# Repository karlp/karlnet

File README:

Hi! This is the karlnet source tree.
karlnet consists of nodes, which are (normally) battery powered sensor devices, transmitting data at some
interval back to a base station.  The base station handles decoding the binary wire formats, and posts all
the data onto a stomp message bus topic. (the base station is a data producer)  Then any consumer that
wishes, simply subscribes to the topic, and receives all data from the network, from the minute the
connect.

common - headers and things for packet definitions, etc
producers - software that can produce data to stick into karlnet, (xbee receiver)
consumers - software that makes use of karlnet data (rrd, webpages, etc)
nodes - firmware that runs on the wireless nodes, and the cad files for each node
eagle - shared files for eagle cad (part libraries)
experiments - uncategorized, or incomplete projects.

python dependencies:
 * Stompy: http://packages.python.org/stompy/
 * python-usb v1.x (you'll have to uninstall 0.4.x, or fiddle with sys.path)
 * python-jsonpickle

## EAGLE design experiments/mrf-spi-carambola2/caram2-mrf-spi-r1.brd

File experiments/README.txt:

1. Name: Karl Palsson

2. Company: n/a

3. Billing address: 

Karl Palsson
Hverfisgata 104c
Reykjavik, 101
Iceland

4. Shipping address: 

same as billing

5. Shipping option: airmail

6. Order: 
    1 DSS panel, panelisation image attached as:  olimex-panelisation-20110107.png

7. For all orders from Europe Union: n/a

8. Payment option: Visa

9. De-panelization with smooth or rough borders (read our FAQ for panelization
to learn what does this means)
   Smooth.  I believe my measurements are correct, and there's room for this.

10. Notes: 

    dresdonbo_v02 uses 0.6mm drills, to make sure that the pad/drill spacing meets your
design rules.

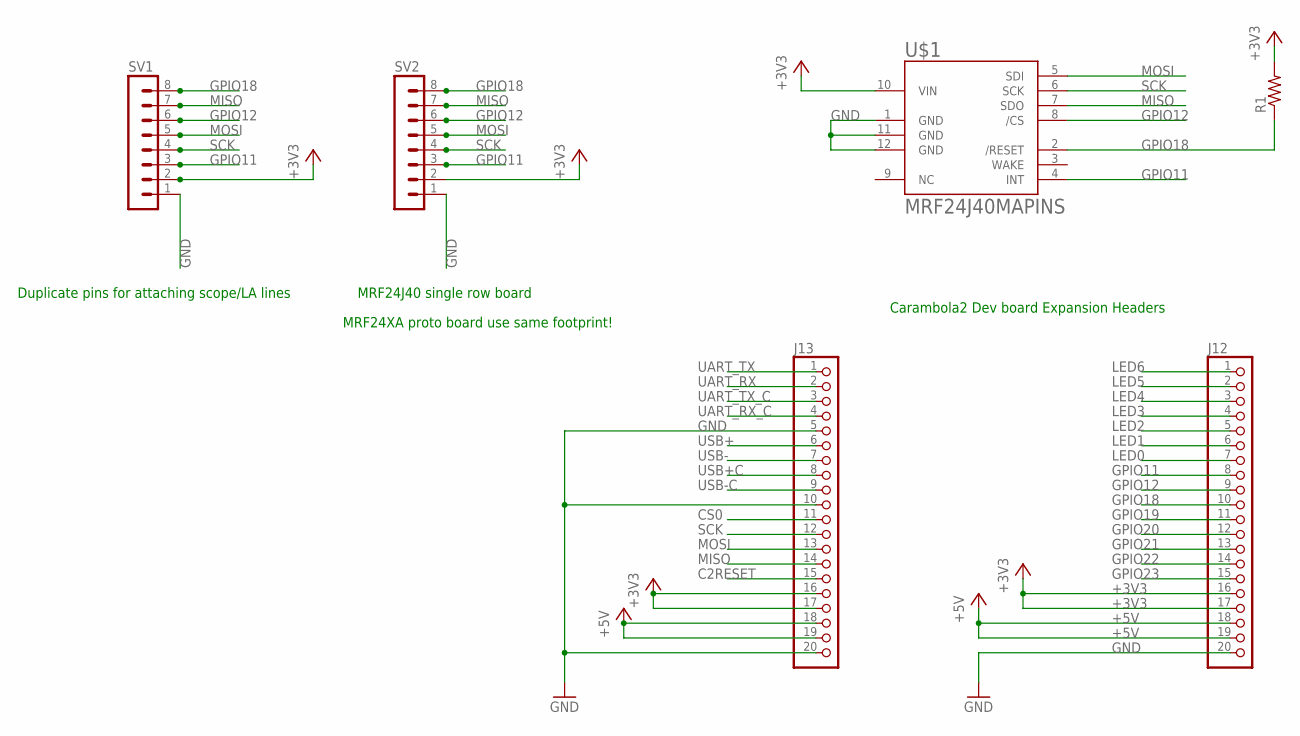
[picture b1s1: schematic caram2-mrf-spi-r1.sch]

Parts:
J12, J13: PINHD-1X20; 1X20
R1: R-US_R0805; R0805
SV1, SV2: MA08-1
U$1: MRF24J40MAPINS; MRF24J40MA

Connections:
+3V3: J12.16, J12.17, J13.16, J13.17, R1.2, SV1.2, SV2.2, U$1.10 (VIN)
+5V: J12.18, J12.19, J13.18, J13.19
C2RESET: J13.15
CS0: J13.11
GND: J12.20, J13.5, J13.10, J13.20, SV1.1, SV2.1, U$1.1 (GND), U$1.11 (GND), U$1.12 (GND)
GPIO11: J12.8, SV1.3, SV2.3, U$1.4 (INT)
GPIO12: J12.9, SV1.6, SV2.6, U$1.8 (/CS)
GPIO18: J12.10, R1.1, SV1.8, SV2.8, U$1.2 (/RESET)
GPIO19: J12.11
GPIO20: J12.12
GPIO21: J12.13
GPIO22: J12.14
GPIO23: J12.15
LED0: J12.7
LED1: J12.6
LED2: J12.5
LED3: J12.4
LED4: J12.3
LED5: J12.2
LED6: J12.1
MISO: J13.14, SV1.7, SV2.7, U$1.7 (SDO)
MOSI: J13.13, SV1.5, SV2.5, U$1.5 (SDI)
SCK: J13.12, SV1.4, SV2.4, U$1.6 (SCK)
UART_RX: J13.2
UART_RX_C: J13.4
UART_TX: J13.1
UART_TX_C: J13.3
USB+: J13.6
USB+C: J13.8
USB-: J13.7
USB-C: J13.9

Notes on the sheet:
MRF24J40 single row board
MRF24XA proto board use same footprint!
Carambola2 Dev board Expansion Headers
Duplicate pins for attaching scope/LA lines

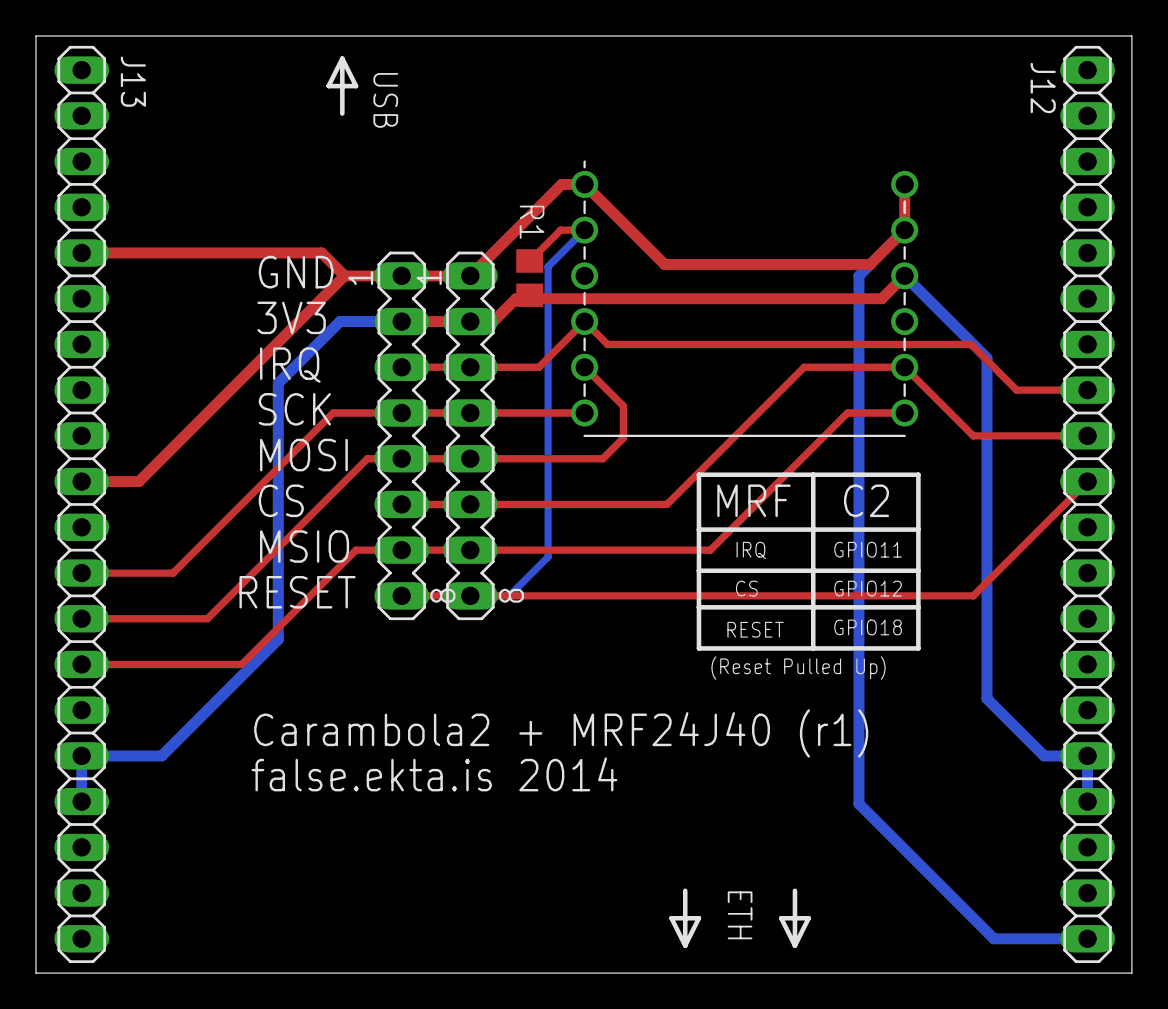
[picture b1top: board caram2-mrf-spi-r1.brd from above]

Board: 2 copper layers, 60.9 x 52.1 mm, 6 parts (0 on the bottom side), 9 nets.

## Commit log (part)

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2010-03-24 Support node 4203, now configured at pachube, and also support artbitrary numbers of sensors (Still no type distinction, and pachube must be manually setup with the descriptions in the right orders) 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
2010-05-06 Adding in a sqlite3 datalogger. Let's _reallly_ keep all this data, not just in an rrd, which needs to be tediously configured in advance for each node. Just save every node's raw sensor data to a bi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
2010-05-18 Restructuring the pjrc supplied files, and the makefiles in preparation for multiple teensy boards
2010-05-18 adding ignores for vim/gvim ~backup files and .swp files
2010-05-19 On linux, at least on ubuntu 9.10, for this particular device at least, you need to detach the kernel driver first...
2010-05-20 Very rough self updating graph, just showing the values for sensor0 on any node's data that's received
2010-05-26 Switching to 8080, which seems to be open from more places. hopefully ;) (Had to change activemq config too)
2010-10-18 Properly put the actual char data to the usb host, rather than a hex printed version of it
2010-10-20 Use avr/power.h clock prescalar tools rather than pjrc bit macros
2010-10-22 Use correct address for wildcards within a topic.
    We started using karlnet/[nodeid] as separate topics for each node, didn't update this consumer
2010-10-22 Add support for decoding tx packets off a serial port
    This makes it easy to hook up the FTDI cable on a node under test to see
    what it's sending out, instead of trying to catch it on the head end of the
    live system
2010-10-23 Sample udev rules file that works for non-sudo avr programming
2010-10-23 Netbeans project files for oew power meter.
2010-10-26 rename directory to more accurately reflect contents of the power monitoring board
2010-10-26 Use a function to do the power meter reading.
    This is far far far from what I call a function, but I was having all sorts of problems getting this to work.
    More to come :|
2010-10-26 Move more global variables inside the function they're used in
2010-10-26 netbeans needs to be told about the change in project directory/name
2010-10-26 8080 is more likely to be reachable by regular browsers.
    Fix the username/password problem on reconnect found in the graph app
2010-11-04 Readme and todo files make it look nicer in github, and are just nicer for future users
2010-11-04 More board level readmes
2010-11-04 Creating a github page for karlp.github.com/karlnet
2010-11-05 proving it works
2010-11-06 Finally got it working to have all the sensors for a node on each node's graph
2010-11-06 Show meaninful labels instead of raw sensor type codes.
2010-11-06 Make the x-axis a time, rather than just an index.
2010-11-07 Update tinytemp firmware to kpacket version 1.
    Pad wire packets out to MAX_SENSORS. For some reason, tinytemp crashed and went
    haywire if I tried to only send two sensors.
2010-11-07 relable variables and use a better constant for the new LM35 sensors
2010-11-07 Udate documentation. (netbeans didn't save automatically enough)
2010-11-09 make graphs by sucking data back from pachube.
    Let google do the heavy lifting, uses http://apps.pachube.com/google_viz/
    but patched locally to allow having more than one graph per page
2010-11-24 Add a new draft of a two channel tiny84 based humidity sensor.
    (Still needs review, plus an LED for the xbee transmit)
2010-11-24 Connect the RX lines to the xbee, just for future flexibility Connect an optional RSSI indicator LED Connect the CTS_ line from the xbee to the last unused attiny pin, just for future flexibility
2010-12-05 Provide a library reader as well as writer.
    Major overhaul of the db writer, proper classes now, should be much easier to pull data out
2010-12-05 Send the proper mime type when we're replying scrip tags for jsonp
2010-12-05 Current config for the tinytemp is a second tmp36 on a probe cable
2010-12-05 When we first see an unknown packet, go and fetch a chunk of historical data from the server for that node.
    Bug: it should then still include the reading that prompted the fetch...
    Bug: flot seems to draw a new line from the origin to the next point after that?!
2010-12-11 Gerbers to be sent to olimex
2010-12-11 Straighten the right edge, WTF happened?
2010-12-21 Add more readme's for better github browsing
2010-12-29 Add very very hacky support for sending out karlnet packets via a serially connected xbee.
    It will NOT stay like this, but I want to keep it in one place while it's still working.
2011-01-04 Stupid netbeans doesn't autosave.
2011-01-22 Adding the "fixed" board and schematic after learning about eagle's moronic "restring" These are the boards that olimex is actually making. They rejected v02.
2011-01-24 Added support for the atmega32u4 (and presumably 16u4) to the "standard" avr uart library.
    Only tested with RX so far, that's all I need.
2011-01-27 Add lufa as a git submodule
2011-01-28 Don't need this old netbeans makefile
2011-02-02 Make the logging and stomp posting based on a runtime flag, so I can stop having outstanding code changes in my tree
2011-02-02 Update docs a bit more
2011-02-02 Add a local receiver to parse the "raw" kpackets from the second pipeline
    Needed some ugly hacks to make the raw serial data piped out this way to look the same
    as how it comes in from the xbee over a ftdi cable. Byte order sux0rs
2011-02-02 Remove duplicate code.
    Only difference was the name of the "start" routine, which I've just put back to the original name, matching
    the definitions
2011-02-03 Reference LUFA libraries from outside our git tree, rather than using git submodules
2011-02-07 Fix frequency counting.
    Original code on teensy humi was actually wrong, sizeof(unsigned int) is actually only 16 bits on avrs,
    so what I was using as the "working reference" was actually only the lower 16 bits.
    Likewise, the odd behaviour with version and sensor count is because ordering and packing of bit fields in C is
    implementation dependent, and nothing to ever rely on.
2011-02-07 Add what seems to be a viable netbeans project config for the local dual pipeline receiver
2011-02-07 local_raw should not use the same log as justwatchserial
2011-02-08 Add a decoder for scanning the ntc curve files to find the nearest temperature.
    And learn a bit more about python packaging and testing
2011-02-08 We started depending on the message producers adding a timestamp, but the newly hatched serial pipeline receivers weren't doing that.
    Add it back in again, based on the pyhid code.
2011-02-08 Generated an IP restricted api key for pachube uploader.
    (Don't look through the git history!)
2011-02-12 Set the sensor type codes in stone a bit better, and decode more in just watch serial
2011-02-12 Don't explode when you get a zero reading for frequency
2011-02-17 More TODOs
2011-02-17 Replace busy wait with watchdog timer sleep for 4 seconds.
    The busy wait while the frequency counter is gating is still a major
    power hog, drawing ~3mA for a whole second. This will need to be addressed :)
2011-02-17 Remove pointless debug
2011-02-18 Don't crash just because we got a bus packet that wasn't ours!
2011-02-18 Use optparsing to enable test mode cleanly, as learnt in other modules
2011-02-20 Add short_read and long read and write, and a lot of datasheet info for bootstrapping
2011-02-20 Dump rxfifo data whenever a packet is received.
    This works, in that it recognises each packet received, but the rxfifo data doesn't seem to match
    what I'm sending.
2011-02-20 No, I was just stupidly using mrf_read_short() with a long address.
    proper rx with the right data now.
2011-02-28 Handle zero length packets by raising a bad packet exception, rather than crashing.
2011-02-28 Gerbers sent to dorkbot pdx for pcb fab
2011-03-02 Add modem status report decoding
2011-05-10 Add the basics for the fridge controller code.
    Nothing much yet.
2011-05-17 Updated schematics to make wiring easier and schematic easier to read.
2011-05-19 Support decoding of reports from the fridge controller.
    Support the other endian of the mrf24j chip.
    Add threshold and min runtime config for the relay output. (Verified with a light!)
    While the EEPROM config block works, I don't have the rf reception working yet. The tiny84 is a bit
    light on debugging tools (other than the rf link under test) so I think I'll wire this back up on a
    teensy board and get some printout of what's going on....
2011-05-23 Update config for sensor display with the fridge controller.
2011-05-29 keeping eagle happy
2011-05-29 Unsure what's changed. Eagle doesn't do diffs very well :(
2011-05-29 Use stdio, instead of pjrc's debug print on the teensy board.
    We have more than enough flash space, and it's just more pleasant to have printf.
2011-05-29 Trying to make netbeans a bit smarter by providing some preprocessor definitions.
2011-05-29 Update netbeans project files after the project rename.
2011-05-29 For the demo, use more flash space to have a nicer printf. We don't need the space that badly.
2011-05-29 Update mega128rfA1 demo code to hook stdio up on both UART0 and UART1.
    Required a minor change to Peter Fleury's avr uart library.
2012-05-02 Relabel pin definitions to make internal code consistent.
    This was part of the work to split the mrf24j40 library out of AVR
2012-05-05 Keep eagle happy
2012-05-05 No need for whole scripts to watch messages.
    We're using mqtt, it's all easier.
2012-05-14 Proposed board for stm32 based mrf node
    STM32F100, lqfp48
    RHT03 for local humidity and temp
    2 jacks for analog inputs (temp probes)
    mrf24j40ma for comms
    mcp1623/1640 SMPS
    designed for a 2xAA batterholder on the flip side
2012-07-02 WIP for dht reads...
2012-07-24 Add channel 1/2 labels.
    Fix version text to not look "3 dimension" something or other
2012-09-21 Support variable mqtt host for the consumer
2012-10-09 Updated boards for v3f
2012-10-09 More notes on board changes
2012-10-28 Tidied up and almost final verified v4 board.
    Hope the pinouts are right, looks good on board, not sure about in the library.
    Stupid eagle binary formats and branches.
2012-11-21 Fix Kycon STX3120 footprint silk and extra drills
2012-11-21 [boxcar] avoid PC13,14,15 and their current limitations
    Moved the debug led to the other side.
    Text that used to be in copper layer also moved to silk, as this board will
    not be milled, but produced properly.
2013-01-28 [boxcar] remove excessive nastylogging
    nastylogging comes from linux, far too big for this project
2013-01-28 [boxcar] update hardware changelog after first assembly
2013-01-31 Add simrf library as submodule
2013-02-01 Oops, missing 802.15.4 files!
    Pushed already, can't rebase now!
2013-02-03 [boxcar] add simple ADC readings
2013-02-14 [boxcar] start sending to the karlnet
2013-02-21 Only send sensors that are connected
2013-02-24 afkbeer - initial stub code
    Connects to mq and show messages as they arrive. Lots to go, and the
    windows explode as data arrives, but it's a start!
2013-02-26 Funtional sounds being played, but ugly.
2013-03-08 [boxcar] Turn off the radio when not in use
    Power drops from steady 40ma+ to ~12ma. Worthwhile evening.
2013-06-11 Only continue when mqtt is up
2013-09-18 afbkeer: make it work again on fed18?!
    playbin2 started just returning None? docs are awesome in gstreamer.
    experimentally found that playbin worked.
2015-04-04 mosquitto -> paho mqtt
2015-04-04 Don't leave things mixed defines in committed code.
2015-04-05 output-sparkfun: dump data to sparkfun
    No config, just basic poster to sparkfun
2015-04-05 commit old notes on future plans
    Save them into git please..
2015-05-25 output-sparkfun: channel1 is required in the feed
    At least the way we set it up. Fake it if the cable is disconnected.
2015-05-25 boxcar: restore optimization
    No idea why this was turned off.
2015-05-30 gitignore: more project file ignoring
2015-05-30 constify PROGMEM to satisfy gcc's apetite
